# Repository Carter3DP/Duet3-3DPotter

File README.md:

# Duet3-Mainboard-3DP

This board is a fork of the Duet3 6XD with a little of the 6HC. You can find
them here:

[https://github.com/Duet3D/Duet3-Mainboard-6XD](https://github.com/Duet3D/Duet3-Mainboard-6XD)

[https://github.com/Duet3D/Duet3-Mainboard-6HC](https://github.com/Duet3D/Duet3-Mainboard-6HC)

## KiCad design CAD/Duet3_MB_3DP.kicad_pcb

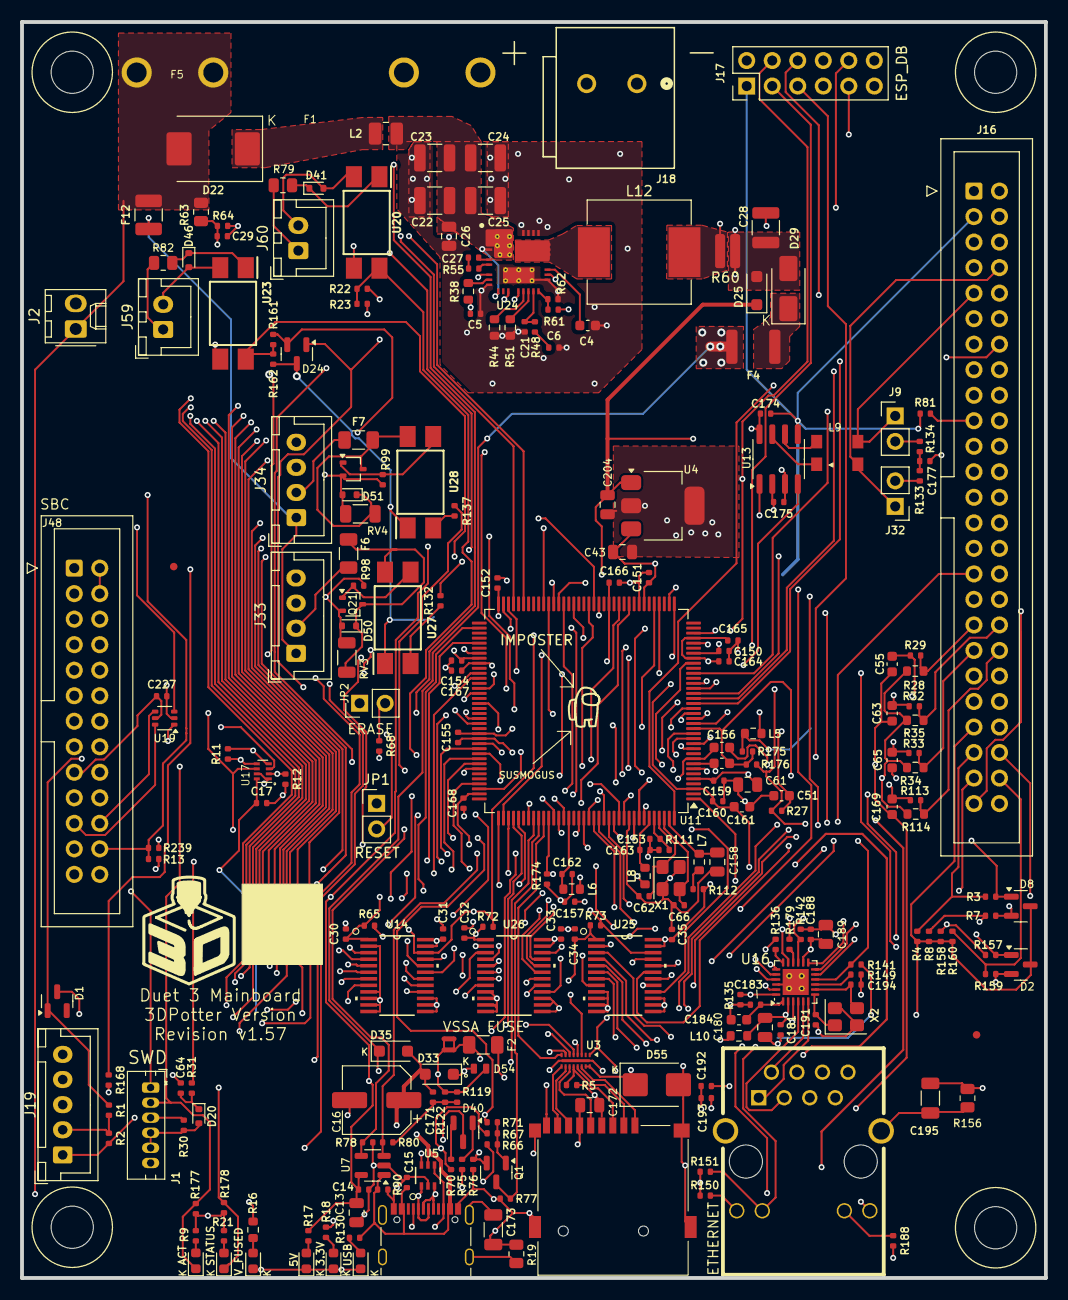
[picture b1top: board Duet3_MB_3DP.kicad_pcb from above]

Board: 4 copper layers, 101.9 x 125.0 mm, 253 parts (1 on the bottom side), 214 nets.

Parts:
C4: 2.2uF 10V; C_0603_1608Metric
C5: 470nF 10V; 0402_1005Metric_NoSilk
C6: 15nF 16V; 0402_1005Metric_NoSilk
C13, C43, C172, C180, C189, C204: 10uF 10V; C_0805_2012Metric
C14, C15, C17, C171, C174, C175, C181, C183, C188, C192, C193, C227: 0.1uF 16V; 0402_1005Metric_NoSilk
C16: 100uF 35V; CP_Elec_6.3x7.7
C21: 300pF 25V; 0402_1005Metric_NoSilk
C22, C23, C24, C25: 4.7uF 100V; C_1210_3225Metric
C26: 100nF 100V; C_0805_2012Metric
C27: 47nF 10V; 0402_1005Metric_NoSilk
C28: 47nF 16V; C_1210_3225Metric
C29, C64: 10nF 10V; 0402_1005Metric_NoSilk
C30, C31, C32, C33, C34, C35, C150, C151, C152, C154, C155, C157, C159, C160, C162, C163, C164, C165, C166, C167, C168: 100nF 16V; 0402_1005Metric_NoSilk
C51, C55, C63, C65, C169, C184, C200: 2.2uF 16V; C_0603_1608Metric
C61, C158: 4.7uF 16V; C_0805_2012Metric
C62, C66, C153: 10pF 50V; 0402_1005Metric_NoSilk
C156, C161: 1uF 25V; C_0603_1608Metric
C173, C195: 1nF 1kV; C_1206_3216Metric
C177: 4.7nF 10V; 0402_1005Metric_NoSilk
C191, C194: 22pF 50V; 0402_1005Metric_NoSilk
D1, D2, D8, D24, D40: BAT54C; SOT-23
D4: BLUE; LED_0603_1608Metric
D5, D7, D23: RED; LED_0603_1608Metric
D6, D42: GREEN; LED_0603_1608Metric
D20, D41, D46, D50, D51: 1N4448WT; D_SOD-523
D22: ACDBC5100-HF; D_SMC
D25, D33, D35: 1A,40V; D_SOD-123F
D29: 3A 40V; D_SMA
D54: D_TVS_5V; DFN1610-2L
D55: D_TVS_3.3V; D_SMB
F1, F5: 01220088Z
F2: VSSA FUSE; Fuse_1206_3216Metric
F4: PTC_3A; Fuse_1812_4532Metric
F6, F7: FUSE 60V 50mA/150mA; Fuse_1206_3216Metric
F12: FUSE 90V 300mA-500mA; Fuse_1210_3225Metric
J1: SWD; JST_ZH_B6B-ZR_1x06_P1.50mm_Vertical
J2: A2543WV-2P; Molex_KK-254_AE-6410-02A_1x02_P2.54mm_Vertical
J9, J32: Conn_01x02; PinHeader_1x02_P2.54mm_Vertical
J16: EXPANSION; IDC-Header_2x25_P2.54mm_Vertical
J17: ESP_DB; PinHeader_2x06_P2.54mm_Vertical
J18: 250-502/000-006; CONN2_250-502&slash_000-006_WAG
J19: A2543WV-5P; JST_XH_B5B-XH-A_1x05_P2.50mm_Vertical
J27: uSD_Socket; uSD_SKT
J33, J34: A2543WV-4P; JST_XH_B4B-XH-A_1x04_P2.50mm_Vertical
J43: USB; USB_C_Receptacle_Valcon_CSP-USC16-TR
J46: ETHERNET; RJ45+MAG
J48: SBC; IDC-Header_2x13_P2.54mm_Vertical
J59, J60: A2543WV-2P; JST_XH_B2B-XH-A_1x02_P2.50mm_Vertical
JP1: RESET; PinHeader_1x02_P2.54mm_Vertical
JP2: ERASE; PinHeader_1x02_P2.54mm_Vertical
L2: 1uH; L_1008_2520Metric
L5, L6, L7, L8, L10: 1K @100Mhz; R_0603_1608Metric
L9: CM Choke; LineKey_CM_Choke_SCW_4532A
L12: 10 uH; L_Vishay_IHLP-4040
M1, M2: FID; Fiducial_0.75mm_Mask1.5mm
M3, M9, M11, M15: MOUNTING; Fixing_M4
NT1, NT2: Net-Tie_2; NetTie-2_SMD_Pad0.5mm
Q1: BC807; SOT-23
Q21, Q22: MMBTA06-7-F; SOT-323_SC-70
R1, R3, R7, R18, R22, R27, R29, R30, R32, R33, R77, R80, R113, R142, R151, R157, R159, R161, R174: 10K; 0402_1005Metric_NoSilk
R2, R4, R8, R11, R12, R13, R81, R122, R158, R160: 27K; 0402_1005Metric_NoSilk
R5, R177, R178: 100K; 0402_1005Metric_NoSilk
R9, R21, R76, R136, R141, R239: 1K; 0402_1005Metric_NoSilk
R16: 120K; R_0603_1608Metric
R17, R130: 5K; 0402_1005Metric_NoSilk
R19, R156: 1M; R_0805_2012Metric
R23, R64, R78, R135, R176: 4.7K; 0402_1005Metric_NoSilk
R28, R34, R35, R114: 2.2K 0.1% 0.2W+; R_0603_1608Metric
R31: 180R; 0402_1005Metric_NoSilk
R38: 100k; R_0603_1608Metric
R44: 41.2K; R_0603_1608Metric
R48: 2.61k; 0402_1005Metric_NoSilk
R51: 53.6K; R_0603_1608Metric
R55: 1 Ohm; 0402_1005Metric_NoSilk
R60: 6 mOhm; R_0612_1632Metric
R61: 52.3k; 0402_1005Metric_NoSilk
R62: 10k; 0402_1005Metric_NoSilk
R63: 120K; R_0805_2012Metric
R65, R72, R73, R119: 47K; 0402_1005Metric_NoSilk
R66, R67: 28.7K; 0402_1005Metric_NoSilk
R68, R98, R99: 2.2K; 0402_1005Metric_NoSilk
R70, R75: 2.87K; 0402_1005Metric_NoSilk
R71: 15K; 0402_1005Metric_NoSilk
R79, R82: 10K 0.25W; R_0805_2012Metric
R90, R132, R137, R150, R168, R188: 470R; 0402_1005Metric_NoSilk
R111: 5.62K; 0402_1005Metric_NoSilk
R112: 2.2R; 0402_1005Metric_NoSilk
R133, R134: 59R; 0402_1005Metric_NoSilk
R149: 6.49K; 0402_1005Metric_NoSilk
R162: 4.7k; 0402_1005Metric_NoSilk
R175: 15R; 0402_1005Metric_NoSilk
R179: 27R; 0402_1005Metric_NoSilk
RV3, RV4: VE1206K121R050; R_1206_3216Metric
TM1: 3DPotter Logo 10x10mm
TM2: Amogus
TP39: VREFP; TestPoint_Pad_D1.5mm
U3: EMIF06; QFN-16L-3.5x1.2mm_P0.4mm
U4: AP7361C-33E-13; SOT-223
U5: RClamp0504FB; SC70_RCLAMP_SEM
U7: AP22816AKEWT; SOT-23-5
U11: ATSAME70Q20B-ANT; LQFP-144_20x20mm_P0.5mm
U13: MCP2542; SOIC-8_3.9x4.9mm_P1.27mm
U14, U25, U26: SN74LVC4245APWR; PW24
U16: KSZ8081RNACA; QFN-24-1EP_4x4mm_P0.5mm_EP2.6x2.6mm_THT
U17: 74LVC2G125; X2-DFN2010-8
U19: 74LVC2G34; SOT-363_SC-70-6
U20, U23, U27, U28: Optoisolator; SOP254P1016X460-4N
U24: LM70860RRXR; RRX0029B-MFG
X1: ECS-120-10-33B-CKM-TR; Crystal_SMD_3225-4Pin_3.2x2.5mm
X2: 25Mhz; Crystal_SMD_3225-4Pin_3.2x2.5mm

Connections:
5V_EXT: D35.1 (K), F4.1, J16.1, J19.5
5V_INT: C13.1, C14.1, C30.1, C32.1, C34.1, C175.1, C204.1, D25.1 (K), D33.1 (K), D54.1 (K), R17.1, R65.2, R72.2, R73.2, U4.1 (IN), U7.5 (IN), U13.3 (VDD), U14.1 (VCCA), U25.1 (VCCA), U26.1 (VCCA)
5V_SBC: J48.2, J48.4
+3.3V: C17.1, C31.1, C33.1, C35.1, C43.1, C61.1, C150.1, C151.1, C152.1, C154.1, C155.1, C157.1, C159.1, C172.1, C174.1, D1.3, D2.3, D8.3, D24.3, D55.1 (K), J1.3, J16.3, J16.43, J17.1, J19.1, J27.4 (VDD), JP2.1, L5.1 (A), L10.1 (A), R2.2, R4.2, R5.2, R8.2, R9.1, R13.2, R18.1, R21.1, R23.2, R30.2, R81.2, R112.1, R136.1, R141.1, R150.1, R151.1, R158.2, R160.2, R162.2, R177.2, R178.2, U3.15 (VCC), U3.16 (RDATA_VCC), U4.3 (OUT), U11.5 (VDDIN), U11.30 (VDDIO), U11.43 (VDDIO), U11.72 (VDDIO), U11.80 (VDDIO), U11.96 (VDDIO), U11.134 (VDDUTMII), U13.5 (VIO), U14.23 (VCCB), U14.24 (VCCB), U17.8 (VCC), U25.23 (VCCB), U25.24 (VCCB), U26.23 (VCCB), U26.24 (VCCB), U27.1, U28.1
/Comms/CAN1H_C: L9.1, U13.7 (CANH)
/Comms/CAN1L_C: L9.4, U13.6 (CANL)
/Comms/CLK: J27.5 (CLK), U3.11 (CLK)
/Comms/CMD: J27.3 (CMD), R5.1, U3.12 (CMD)
/Comms/DAT0: J27.7 (DAT0/DO), U3.10 (Data0)
/Comms/DAT1: J27.8 (DAT1), U3.9 (Data1)
/Comms/DAT2: J27.1 (DAT2), U3.14 (Data2)
/Comms/DAT3: J27.2 (DAT3), U3.13 (Data3)
/Comms/LED0: J46.10 (LEDG_K), R151.2, U16.23 (LED0)
/Comms/RD+: J46.3 (RD+), U16.4 (RXP)
/Comms/RD-: J46.6 (RD-), U16.3 (RXM)
/Comms/REF_CLK: R179.2, U16.16 (REF_CLK)
/Comms/REXT: R149.1, U16.9 (REXT)
/Comms/SHIELD_GND: C195.2, J46.8 (GND), J46.13 (SHIELD), J46.14 (SHIELD), R156.2
/Comms/TD+: J46.1 (TD+), U16.6 (TXP)
/Comms/TD-: J46.2 (TD-), U16.5 (TXM)
/Comms/VDDA_3V3: C180.1, C181.1, C188.1, C189.1, L10.2 (B), U16.2 (VDDA_3V3), U16.14 (VDDIO)
/Comms/VDD_1V2: C183.1, C184.1, U16.1 (VDD_1V2)
/Comms/XI: C194.2, U16.8 (XI), X2.3
/Comms/XO: C191.2, U16.7 (XO), X2.1
/Comms/can1_term_c: C177.2, R133.2, R134.1
/Comms/cc1d: D40.2, R70.2
/Comms/cc2d: D40.1, R75.2
/Comms/intrp: R136.2, U16.18 (INTRP)
/Comms/q1b: Q1.1 (B), R66.1, R67.1, R71.2
/Comms/usbce: C173.1, J43.S1 (SHIELD), R19.1
/IO/opt_io5_i_p: D46.1 (K), R82.2, U23.1
/IO/opt_io5_o: D50.1 (K), F6.2, Q21.3 (C), RV3.1, U27.4
/IO/opt_io5_oc: Q21.1 (B), R98.2, U27.3
/IO/opt_io5_pin: R132.1, U27.2
/IO/opt_io6_i_p: D41.1 (K), R79.2, U20.1
/IO/opt_io6_o: D51.1 (K), F7.2, Q22.3 (C), RV4.1, U28.4
/IO/opt_io6_oc: Q22.1 (B), R99.2, U28.3
/IO/opt_io6_pin: R137.1, U28.2
/Power/5V_Common: C28.1, D25.2 (A), D29.2 (A), R60.2, R61.2, U24.6 (BIAS), U24.12 (VOUT)
/Power/5v_ext_fuse: D29.1 (K), F4.2
/Power/C6_1: C6.1, R48.1
/Power/C27_1: C27.1, R55.1
/Power/CAP_VCC: C4.1, U24.19 (VCC)
/Power/CBOOT: C27.2, U24.4 (CBOOT)
/Power/CONFIG: R44.2, U24.13 (CONFIG)
/Power/EXTCOMP: C21.1, R48.2, U24.15 (EXTCOMP)
/Power/FB: R61.1, R62.2, U24.16 (FB)
/Power/ISNS+: L12.2, R60.1, U24.11 (ISNS+)
/Power/L2: D22.1 (K), L2.1 (A)
/Power/PG_SYNCOUT: R38.2, U24.7 (PG_SYNCOUT)
/Power/RT: R51.2, U24.14 (RT)
/Power/SW: L12.1, U24.20 (SW1), U24.21 (SW2), U24.22 (SW3)
/Power/SW4: R55.2, U24.5 (SW4)
/Power/VDDA: C5.1, R38.1, U24.18 (VDDA)
/Power/VIN1: C22.1, C23.1, C24.1, C25.1, C26.1, L2.2 (B), U24.1 (VIN4), U24.2 (VIN5), U24.3 (VIN6), U24.9 (EN_UVLO), U24.27 (VIN1), U24.28 (VIN2), U24.29 (VIN3)
/Processor/IO_0_O: R168.1, U11.53 (PD26)
/Processor/VBG: C153.1, R111.2, U11.140 (VBG)
/Processor/VDDCORE: C160.1, C161.1, C164.1, C165.1, C166.1, C167.1, C168.1, L6.2 (B), L8.2 (B), U11.3 (VDDOUT), U11.29 (VDDCORE), U11.33 (VDDCORE), U11.50 (VDDCORE), U11.81 (VDDCORE), U11.107 (VDDCORE)
/Processor/VDDPLL: C162.1, L6.1 (A), U11.123 (VDDPLL)
/Processor/VDDPLLUSB: C158.1, L7.1 (A), U11.143 (VDDPLLUSB)
/Processor/VDDUTMIC: C163.1, L8.1 (A), U11.139 (VDDUTMIC)
/Processor/XIN: C66.1, U11.142 (PB9), X1.3
/Processor/XOUT: C62.1, U11.141 (PB8), X1.1
/Processor/rst: C64.1, D20.1 (K), R31.2
CAN1_H: J16.8, J32.1, L9.2
CAN1_L: J9.1, J16.9, L9.3
CANRX1: U11.17 (PC12), U13.4 (RXD)
CANTX1: U11.92 (PD12), U13.1 (TXD)
CC1: J43.A5 (CC1), R67.2, R70.1, U5.6
CC2: J43.B5 (CC2), R66.2, R75.1, U5.4
D0_DIR: J16.6, U26.4 (A2)
D0_EN: J16.7, U26.3 (A1)
D1_DIR: J16.11, U26.5 (A3)
D1_EN: J16.12, U26.6 (A4)
D2_DIR: J16.16, U14.7 (A5)
D2_EN: J16.17, U14.8 (A6)
D3_DIR: J16.21, U26.7 (A5)
D3_EN: J16.22, U26.8 (A6)
D4_DIR: J16.26, U14.5 (A3)
D4_EN: J16.27, U14.6 (A4)
D5_DIR: J16.32, U14.3 (A1)
D5_EN: J16.33, U14.4 (A2)
DRIVER_0_DIR: U11.109 (PB5), U26.20 (B2)
DRIVER_0_EN: U11.105 (PB4), U26.21 (B1)
DRIVER_0_STEP: U11.111 (PC18), U25.21 (B1)
DRIVER_1_DIR: U11.101 (PD10), U26.19 (B3)
DRIVER_1_EN: U11.32 (PA21), U26.18 (B4)
DRIVER_1_STEP: U11.100 (PC16), U25.20 (B2)
DRIVER_2_DIR: U11.77 (PA4), U14.17 (B5)
DRIVER_2_EN: U11.48 (PC7), U14.16 (B6)
DRIVER_2_STEP: U11.127 (PC23), U25.19 (B3)
DRIVER_3_DIR: U11.37 (PA22), U26.17 (B5)
DRIVER_3_EN: U11.46 (PA23), U26.16 (B6)
DRIVER_3_STEP: U11.38 (PC1), U25.18 (B4)
DRIVER_4_DIR: U11.40 (PC3), U14.19 (B3)
DRIVER_4_EN: U11.99 (PA1), U14.18 (B4)
DRIVER_4_STEP: U11.41 (PC4), U25.17 (B5)
DRIVER_5_DIR: U11.84 (PD14), U14.21 (B1)
DRIVER_5_EN: U11.74 (PD17), U14.20 (B2)
DRIVER_5_STEP: U11.86 (PC9), U25.16 (B6)
D_0_STEP_gated: J16.5, U25.3 (A1)
D_1_STEP_gated: J16.10, U25.4 (A2)
D_2_STEP_gated: J16.15, U25.5 (A3)
D_3_STEP_gated: J16.20, U25.6 (A4)
D_4_STEP_gated: J16.25, U25.7 (A5)
D_5_STEP_gated: J16.31, U25.8 (A6)
EN_DIR_GATE: R65.1, R72.1, U11.57 (PD23), U14.22 (~OE), U26.22 (~OE)
ERASE: JP2.2, R68.1, U11.87 (PB12)
ESP_DATA_RDY: J17.8, U11.93 (PA2)
ESP_EN: J17.10, U11.97 (PC14), U17.1 (1OE), U17.7 (2OE)
EXT_SPI_CK: J16.18, U11.144 (PB13)
EXT_SPI_CS: J16.19, R81.1, U11.26 (PB2)
EXT_SPI_DI: J16.14, U11.21 (PB0)
EXT_SPI_DO: J16.13, U11.20 (PB1)
GMDC: U11.113 (PD8), U16.11 (MDC)
GMDIO: R141.2, U11.110 (PD9), U16.10 (MDIO)
GND: C4.2, C5.2, C6.2, C13.2, C14.2, C15.2, C16.2, C17.2, C21.2, C22.2, C23.2, C24.2, C25.2, C26.2, C28.2, C29.2, C30.2, C31.2, C32.2, C33.2, C34.2, C35.2, C43.2, C51.2, C61.2, C62.2, C64.2, C66.2, C150.2, C151.2, C152.2, C153.2, C154.2, C155.2, C157.2, C158.2, C159.2, C160.2, C161.2, C162.2, C163.2, C164.2, C165.2, C166.2, C167.2, C168.2, C171.2, C172.2, C173.2, C174.2, C175.2, C177.1, C180.2, C181.2, C183.2, C184.2, C188.2, C189.2, C191.1, C192.2, C193.2, C194.1, C195.1, C204.2, C227.2, D4.1 (K), D5.1 (K), D6.1 (K), D23.1 (K), D54.2 (A), D55.2 (A), J1.6, J2.2, J16.2, J16.30, J16.42, J17.2, J17.12, J18.1, J19.3, J27.6 (GND), J27.G (GND), J33.4, J34.4, J43.A1 (GND), J43.A12 (GND), J43.B1 (GND), J43.B12 (GND), J48.6, J48.9, J48.14, J48.20, J48.25, JP1.1, NT1.2, NT2.2, R11.2, R12.2, R19.2, R44.1, R51.1, R62.1, R64.2, R68.2, R76.2, R77.2, R78.2, R90.2, R111.1, R119.2, R135.2, R142.2, R149.2, R156.1, R174.2, R188.2, U3.PAD (GND), U4.2 (GND), U4.4 (GND), U5.2, U7.2 (GND), U11.44 (GND), U11.61 (GND), U11.95 (GND), U11.115 (GND), U11.135 (GND), U11.138 (GND), U13.2 (VSS), U13.8 (S), U14.2 (DIR), U14.9 (A7), U14.10 (A8), U14.11 (GND), U14.12 (GND), U14.13 (GND), U14.14 (B8), U14.15 (B7), U16.22 (GND1), U16.25 (GND2), U17.4 (GND), U19.2 (GND), U20.3, U23.3, U24.8 (PFM_SYNCIN), U24.17 (AGND), U24.23 (PGND1), U24.24 (PGND2), U24.25 (PGND3), U24.26 (PGND4), U24.30 (PGND), U25.2 (DIR), U25.9 (A7), U25.10 (A8), U25.11 (GND), U25.12 (GND), U25.13 (GND), U25.14 (B8), U25.15 (B7), U26.2 (DIR), U26.9 (A7), U26.10 (A8), U26.11 (GND), U26.12 (GND), U26.13 (GND), U26.14 (B8), U26.15 (B7), X1.2, X1.4, X2.2, X2.4
GRX0: U11.125 (PD5), U16.13 (RXD0)
GRX1: U11.121 (PD6), U16.12 (RXD1)
GRXDV: R142.1, U11.126 (PD4), U16.15 (CRS_RV)
GRXER: R174.1, U11.119 (PD7), U16.17 (RXER)
GTX0: U11.131 (PD2), U16.20 (TXD0)
GTX1: U11.128 (PD3), U16.21 (TXD1)
GTXCK: R179.1, U11.1 (PD0)
GTXEN: U11.132 (PD1), U16.19 (TXEN)
HSDN: J43.A7 (D-), J43.B7 (D-), U5.1, U11.136 (HSDM)
HSDP: J43.A6 (D+), J43.B6 (D+), U5.3, U11.137 (HSDP)
IO_0: D1.1, R1.1, U11.52 (PD25)
IO_0_IN: J19.2, R1.2, R2.1
IO_0_OUT: J19.4, R168.2
IO_1: D8.1, R3.1, U11.106 (PD15)
IO_1_IN: J16.45, R3.2, R4.1
IO_2: D8.2, R7.1, U11.71 (PD28)
IO_2_IN: J16.46, R7.2, R8.1
IO_3: D2.1, R157.1, U11.28 (PE5)
IO_3_IN: J16.47, R157.2, R158.1
IO_4: D2.2, R159.1, U11.34 (PD30)
IO_4_IN: J16.48, R159.2, R160.1
IO_5: D24.2, R161.1, U11.23 (PA19)
IO_5_IN: J16.49, R161.2, R162.1, U23.4
IO_5_IN_ISO_NEG: D46.2 (A), J59.2, U23.2
IO_5_IN_ISO_POS: J59.1, R82.1
IO_5_OUT_ISO: R132.2, U11.63 (PD21)
IO_5_OUT_ISO_NEG: D50.2 (A), J33.3, Q21.2 (E), R98.1, RV3.2
IO_5_OUT_ISO_POS: F6.1, J33.2
IO_6: D24.1, R22.1, U11.24 (PA18)
IO_6_IN: J16.50, R22.2, R23.1, U20.4
IO_6_IN_ISO_NEG: D41.2 (A), J60.2, U20.2
IO_6_IN_ISO_POS: J60.1, R79.1
IO_6_OUT_ISO: R137.2, U11.102 (PA0)
IO_6_OUT_ISO_NEG: D51.2 (A), J34.3, Q22.2 (E), R99.1, RV4.2
IO_6_OUT_ISO_POS: F7.1, J34.2
MCCDA: U3.5 (SDCMD), U11.112 (PA28)
MCCK: U3.6 (SDClk), U11.59 (PA25)
MCDA0: U3.7 (SDData0), U11.116 (PA30)
MCDA1: U3.8 (SDData1), U11.118 (PA31)
MCDA2: U3.3 (SDData2), U11.62 (PA26)
MCDA3: U3.4 (SDData3), U11.70 (PA27)
unnamed: D4.2 (A), R16.2
unnamed: D5.2 (A), R17.2
unnamed: D6.2 (A), R18.2
unnamed: D7.2 (A), R21.2
unnamed: D23.2 (A), R130.2
unnamed: D42.2 (A), R9.2
unnamed: J9.2, R134.2
unnamed: J32.2, R133.1
unnamed: J46.9 (LEDG_A), R150.2
unnamed: J46.11 (LEDY_K), R188.1
unnamed: C193.1, J46.5 (RCT)
unnamed: C192.1, J46.4 (TCT)
unnamed: L7.2 (B), R112.2
PHY_RESET: J46.12 (LEDY_A), R135.1, U11.98 (PD11), U16.24 (~RST)
RESET: D20.2 (A), J1.4, J1.5, R30.1, U11.83 (NRST)
RESET_EXT: J16.44, JP1.2, R31.1
SBC_3.3V: C227.1, J48.17, U19.5 (VCC)
SD_CD: J27.9 (Card_Detect), U3.1 (CD), U11.129 (PA29)
SPI1_CS0: J17.6, J48.24, R13.1, R239.1
SPI1_DATA_RDY: J17.4, U11.7 (PE2), U19.3
SPI1_DATA_RDY_BUFF: J48.22, U19.4
SPI1_MISO: J17.5, U11.13 (PC26), U19.1
SPI1_MISO_BUFF: J48.21, U19.6
SPI1_MOSI: J48.19, R11.1, U17.5 (2A)
SPI1_MOSI_BUFF: J17.3, U11.12 (PC27), U17.3 (2Y)
SPI1_SPCK: J48.23, R12.1, U17.2 (1A)
SPI1_SPCK_BUFF: J17.7, U11.130 (PC24), U17.6 (1Y)
STEP_GATE: R73.1, U11.60 (PD22), U25.22 (~OE)
SWCLK: D42.1 (K), J1.2, R177.1, U11.89 (PB7)
SWDIO: D7.1 (K), J1.1, R178.1, U11.79 (PB6)
TEMP_0: C55.1, R29.2, U11.18 (PC15)
TEMP_1: C63.1, R32.2, U11.16 (PC29)
TEMP_2: C65.1, R33.2, U11.11 (PC0)
TEMP_3: C169.1, R113.2, U11.14 (PC31)
THERMISTOR_0: J16.35, R28.2, R29.1
THERMISTOR_1: J16.36, R32.1, R35.2
THERMISTOR_2: J16.37, R33.1, R34.2
THERMISTOR_3: J16.38, R113.1, R114.2
URXD4: J17.11, U11.69 (PD18)
USB_PWR_EN: R78.1, U7.4 (~EN), U11.54 (PC6)
USB_STATE: D40.3, Q1.2 (E), R71.1, R76.1, U11.120 (PC20)
USB_UFP_DETECT: Q1.3 (C), R77.1, U11.117 (PC19)
UTXD4: J17.9, U11.67 (PD19)
VBUS: C15.1, C16.1, D33.2 (A), D35.2 (A), J43.A4 (VBUS), J43.A9 (VBUS), J43.B4 (VBUS), J43.B9 (VBUS), R90.1, R122.1, R130.1, U5.5, U7.1 (OUT)
VBUS_DETECT: C171.1, R80.1, R119.1, R122.2
VIN_POWER_MON: C29.1, R63.2, R64.1, U11.22 (PA20)
VREFN: C55.2, C63.2, C65.2, C156.2, C169.2, C200.2, F2.2, NT1.1, NT2.1, U11.8 (VREFN)
VREFP: C156.1, L5.2 (B), R175.1, TP39.1, U11.9 (VREFP)
VREF_MON: C200.1, R28.1, R34.1, R35.1, R114.1, R175.2, R176.1, U11.15 (PC30)
VSSA: F2.1, J16.40, R27.1, R176.2
VSSA_MON: C51.1, R27.2, U11.19 (PC13)
V_FUSED: D22.2 (A), F5.1, F12.2, J2.1, R16.1, R63.1
V_FUSED_IO: F12.1, J33.1, J34.1
V_IN: F1.1, J18.2
spi1cs0: R239.2, U11.133 (PC25)
~FLG: R80.2, U7.3 (~FLG), U11.122 (PC21)

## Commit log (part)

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2025-06-19 Add Custom Board
2025-06-25 Upload Pinout
2025-07-02 Fix labels
2025-07-25 removed old files from the 6XD, other cleanup
    `pinout.txt` is outdated.
    If you need the files from the 6XD, there's a link in `README.txt`.
    I removed the `.kicad_prl` file. It stores things like "which layer is currently visible".
2025-07-25 WIP redoing board for new print
    Removed version resistors.
    Added pull-up on CMD.
    Working on motors, not routed.
    Added local library for custom parts.
    Ran auto-cleanup of traces and vias (supervised).
2025-07-29 motors have been routed
2025-07-29 update processor order info
2025-07-31 update led resistors
2025-08-25 Moved Traces and Final Prep before Batch 2
2025-08-26 Change/Fix Ferrite Beads
    L6-L8 Changed back to original values, no clue why I changed them in the first place
2025-08-27 Add Alternative Part
    YI321611G800-6R0T is a valid replacement for UPB321611T-800Y-N (L4)
2025-08-27 Delete CAD/production directory
    Remove production files
2025-08-28 Replace Obsolete Parts
    It appears that taiyo yuden is phasing out all BK1608 series ferrite beads, changing L5-L8 back to GZ1608D102TF for now.
2025-08-28 V
    Same change as last commit, forgot to save PCB schematic
2025-10-21 TODO: Finish LM5013, find replacement for TS30041
2025-11-10 Remove 12V Buck Converter
    No need for it, unnecessarily complicates design, plus I dont feel like designing 2 Buck Converter layouts
2025-11-10 Started LM70860
    New 5V 6A (built for 4A) buck dc/dc converter, higher range of input voltage (4.5V-80V), built for 12V-75V according to https://webench.ti.com/power-designer/switching-regulator/customize/3?VinMin=12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
2025-11-11 LM70860 Components layed out
    Still need to connect voltage monitor and make sure all components can handle higher voltage
2025-11-11 Schematic 90%
    Still need VIN_POWER_MON and the voltage divider for it, I need to ask robert what voltages are input through there
2025-11-13 LM70860 Schematic: DONE
    Schematic Finished, physical layout next
2025-11-13 PCB Layout Started
    Current sensing, PG_SYNCOUT to VDDA to GND, CBOOT, Feedback are done! Fuse holder is laid out, but now we need a new power terminal, most likely changing to 250-502/000-006 from WAGO.
2025-11-14 New VIN Connector added
2025-11-14 PCB Done
    As far as I am aware, everything is done, still needs to be run through JLCDFM.
2025-11-14 Update Revision
2025-11-14 Final Touches?
    Top Surface ground plane around LM70860 with star via stitching and some changes for ease of manufacturing.
2025-11-17 Misc. QOL
    Moved some vias around, added some vias, etc.
    Board passed DFM.
2025-11-17 QOL
    Added a buttload of 3d models, 3d model of board is now usable. Also saved a lot of missing symbols and footprints, which are available in the 3DPotter Library.
2025-11-17 Started SN74LVC4245APWR
    This chip is a dedicated 3v3-5v converter, 24 mA output
2025-11-18 Finish SN74LVC4245APWR schematic
    Also adds a new pin to the mcu, "EN_DIR_GATE" serves same function as "STEP_GATE" this is necessary for the SN74LVC to power up safely. Pin is driven low to enable the device.
2025-11-19 Updated output capacitor(s) to reflect page 32 of the datasheet
    Also left some comments on cap placement
2025-11-19 Removed pull-up resistors on motor drivers and corresponding pin on the processor
    also added some misc comments
    I will ask one of my professors about the pull up resistors
2025-11-19 Removed step gate pull-down on processor page
2025-11-19 12 Unconnected left
    Almost done :) Brian fried
2025-11-19 11 Unconnected
    Took me while to make little progress, all because only now have I realized how bad FreeRouting's pathfinding is. So I redid a lot of the traces, bringing them all along a single path clockwise aroun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
2025-11-19 6 Unconnected
2025-11-19 Done
    Just needs DFM check then it should be ready to send to JLC
2025-11-20 update comments on power sheet
2025-11-20 remove the other 3 output capacitors
    now it's back to the way carter had it, except the label is fixed
2025-11-20 Misc Changes
2025-11-20 Color
2025-11-20 Remove Step gate
2025-11-20 So much QOL
    The boards design is shit. I wonder whose fault that is?
2025-11-21 remove step gate pull down resistor
    change D22 to the correct manufacturer part number
2025-11-24 Useless push
2025-11-27 No physical board changes
    Update a datasheet
    removed a comment (Carter reworked the libraries a while - thanks Carter)
2025-12-09 Misc Resistor changes
2025-12-15 Fix Part Name
2025-12-22 Wago confuses me
2025-12-29 OOPS, switched the symbols for psoitive and negative
2026-01-02 Pin Changes / Misc
    Changing some pins around so I have a chip select
    Processor Pins:
    PC28 ---> PA9 (Driver_2_Step)
    PC29[AFE1_AD4] ---> PB1[AFE1_AD0] (TEMP_1)
    PC28 -> spi1cs1
    PC29 -> spi1cs2 (Unused as of now)
2026-01-02 WIP PCB layout
    This is gonna take a little time
2026-01-02 Silkscreen
2026-01-06 Board Finished
    Board has been slightly modified to add SPI to the BBC.
    A lot of library mismatch/ not found errors were fixed. Only errors that exist currently are all related to the silkscreen edges on all 0402 components.
2026-01-19 move driver 2 step to be on the same port as the others
    this is moderately important (not critical, but better for software reasons)
    also I added the silkscreen issues to 'ignore'
    also routed the pin change
2026-01-19 REVERTED BRANCH
    Files got mega corrupted, I reverted to commit e998203. I made roberts changes in this one, so D2 Step is on PC23.
2026-02-17 V1.55 Pre Maufacturing
    Final change for 1.55, changed connectors to jst due to board height issues with the stepper boards
    DFM passed
2026-06-02 Update Revision 1.56
    1.56 Should be production board that is going on all scara* and cartesian printers. 1.56 is a final check that everything is silkscreened properly and all connectors are the correct ones.
    *Not all scaras. Only scara that does not have this board should be Jarret Gross' scara
2026-06-11 Finalize changes for 1.56
    LCSC and P/N updated for excessively out of stock parts.
    Silkscreen changes so no more DRC errors
2026-06-11 Forgot to save
    Same changes as last commit, I forgot to save before pushing
